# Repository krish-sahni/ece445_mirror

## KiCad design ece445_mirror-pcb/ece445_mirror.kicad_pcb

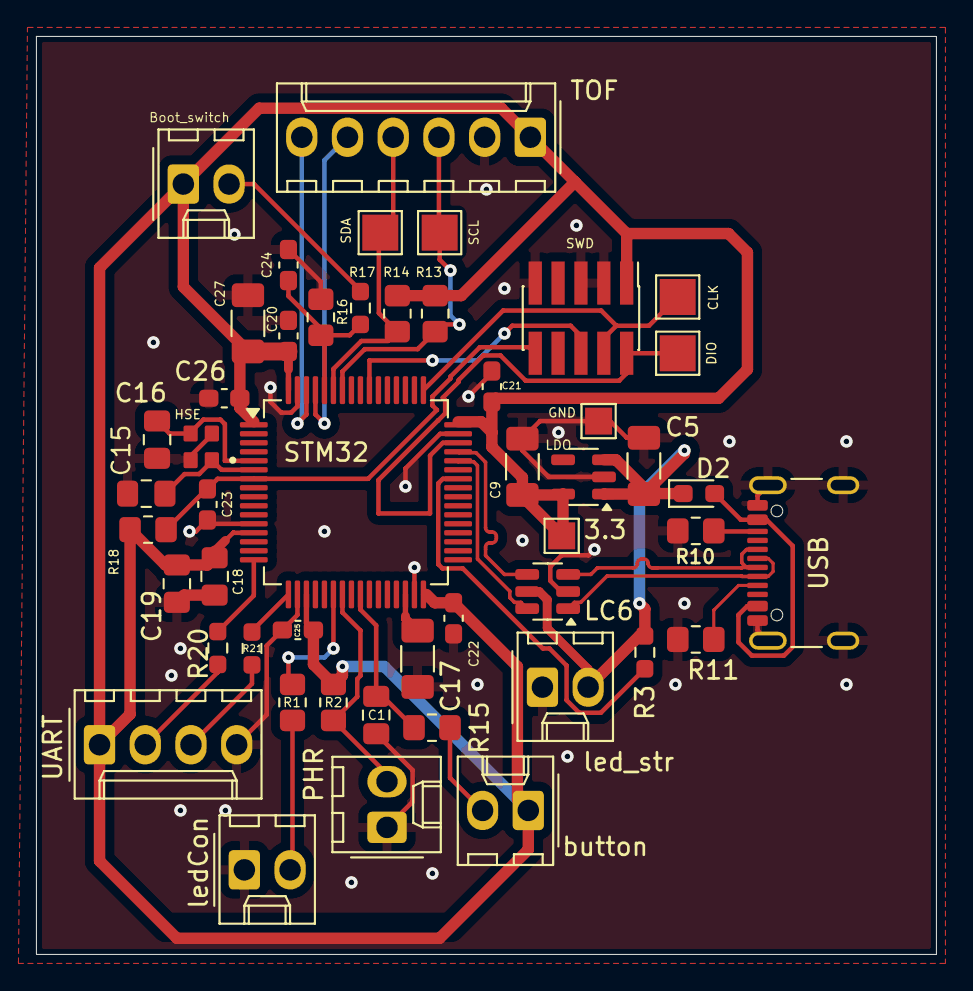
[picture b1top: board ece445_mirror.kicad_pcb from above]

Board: 2 copper layers, 50.0 x 51.0 mm, 49 parts (0 on the bottom side), 33 nets.

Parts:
3.3: TestPoint; TestPoint_Pad_1.5x1.5mm
Boot_switch: boot_switch; Molex_KK-254_AE-6410-02A_1x02_P2.54mm_Vertical
C1, C18: 1u; C_0805_2012Metric_Pad1.18x1.45mm_HandSolder
C5, C9, C27: 4.7u; C_1206_3216Metric_Pad1.33x1.80mm_HandSolder
C15, C16: 10p; C_0805_2012Metric_Pad1.18x1.45mm_HandSolder
C17: 2.2u; C_1206_3216Metric_Pad1.33x1.80mm_HandSolder
C19: 10n; C_0805_2012Metric_Pad1.18x1.45mm_HandSolder
C20, C21, C22, C23, C24, C25, C26: 100n; C_0603_1608Metric_Pad1.08x0.95mm_HandSolder
CLK: TestPoint; TestPoint_Pad_2.0x2.0mm
D2: D_Schottky; D_0603_1608Metric_Pad1.05x0.95mm_HandSolder
DIO: TestPoint; TestPoint_Pad_2.0x2.0mm
GND: TestPoint; TestPoint_Pad_1.5x1.5mm
HSE: 25MHz; OSCCC200X160X50N
LC6: USBLC6-2SC6; SOT-23-6
LDO: AP2112K-3.3; SOT-23-5
PHR: Photoresistor; Molex_KK-254_AE-6410-02A_1x02_P2.54mm_Vertical
R1, R2: 1k; R_0805_2012Metric_Pad1.20x1.40mm_HandSolder
R3, R17, R20, R21: 220R; R_0603_1608Metric_Pad0.98x0.95mm_HandSolder
R10, R11, R13, R14, R18: 5k1; R_0805_2012Metric_Pad1.20x1.40mm_HandSolder
R15, R16: 10k; R_0805_2012Metric_Pad1.20x1.40mm_HandSolder
SCL: TestPoint; TestPoint_Pad_2.0x2.0mm
SDA: TestPoint; TestPoint_Pad_2.0x2.0mm
STM32: STM32F401RBTx; LQFP-64_10x10mm_P0.5mm
SWD: Conn_ARM_JTAG_SWD_10; PinHeader_2x05_P1.27mm_Vertical_SMD
TOF: Conn_01x06; Molex_KK-254_AE-6410-06A_1x06_P2.54mm_Vertical
UART: Conn_01x04; Molex_KK-254_AE-6410-04A_1x04_P2.54mm_Vertical
USB: USB_C_Receptacle_USB2.0_14P; USB_C_Receptacle_GCT_USB4105-xx-A_16P_TopMnt_Horizontal
button: button; Molex_KK-254_AE-6410-02A_1x02_P2.54mm_Vertical
ledCon: LED_CONN; Molex_KK-254_AE-6410-02A_1x02_P2.54mm_Vertical
led_str: LED_STRIP; Molex_KK-254_AE-6410-02A_1x02_P2.54mm_Vertical

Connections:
+3.3V: 3.3.1, Boot_switch.1, C9.1, C18.1, C19.1, C20.1, C21.1, C22.1, C25.1, C26.1, C27.1, LDO.5 (VOUT), R2.2, R13.1, R14.2, R18.1, STM32.1 (VBAT), STM32.13 (VREF+), STM32.19 (VDD), STM32.32 (VDD), STM32.48 (VDD), STM32.64 (VDD), SWD.1 (VTref), TOF.1, UART.1, button.1
+5V: C5.1, D2.1 (K), LC6.5 (VBUS), LDO.1 (VIN), LDO.3 (EN), R3.1, led_str.2
/BOOT0: C24.1, R16.1, R17.1, STM32.60 (BOOT0)
/HSE_in: C16.1, HSE.3, STM32.5 (PH0)
/HSE_out: C15.1, HSE.1, STM32.6 (PH1)
/I2C_SCL: R13.2, SCL.1, STM32.58 (PB6), TOF.3
/I2C_SDA: R14.1, SDA.1, STM32.59 (PB7), TOF.4
/LED_A: R1.2, STM32.22 (PA6)
/LED_STRIP: R3.2, STM32.42 (PA9)
/SWD_CLK: CLK.1, STM32.49 (PA14), SWD.4 (SWCLK/TCK)
/SWD_DIO: DIO.1, STM32.46 (PA13), SWD.2 (SWDIO/TMS)
/SWD_NRST: C23.1, R18.2, STM32.7 (NRST), SWD.10 (~RESET)
/SWD_TRC: STM32.55 (PB3), SWD.6 (SWO/TDO)
/TOF_GPIO: STM32.62 (PB9), TOF.6
/TOF_XSHUT: STM32.61 (PB8), TOF.5
/UART_RX: R21.2, STM32.17 (PA3)
/UART_RXC: R21.1, UART.3
/UART_TX: R20.2, STM32.16 (PA2)
/UART_TXC: R20.1, UART.2
/USBC_D+: LC6.3 (I/O2), USB.A6 (D+), USB.B6 (D+)
/USBC_D-: LC6.1 (I/O1), USB.A7 (D-), USB.B7 (D-)
/USB_CC1: R11.1, USB.A5 (CC1)
/USB_CC2: R10.1, USB.B5 (CC2)
/USB_D+: LC6.4 (I/O2), STM32.45 (PA12)
/USB_D-: LC6.6 (I/O1), STM32.44 (PA11)
GND: C1.2, C5.2, C9.2, C15.2, C16.2, C17.2, C18.2, C19.2, C20.2, C21.2, C22.2, C23.2, C24.2, C25.2, C26.2, C27.2, GND.1, HSE.2, HSE.4, LC6.2 (GND), LDO.2 (GND), PHR.1, R10.2, R11.2, R16.2, STM32.12 (VSSA), STM32.18 (VSS), STM32.31 (VSS), STM32.47 (VSS), STM32.63 (VSS), SWD.3 (GND), SWD.5 (GND), SWD.9 (GNDDetect), TOF.2, UART.4, USB.A1 (GND), USB.A12 (GND), USB.B1 (GND), USB.B12 (GND), USB.S1 (SHIELD), ledCon.1, led_str.1
unnamed: D2.2 (A), USB.A4 (VBUS), USB.A9 (VBUS), USB.B4 (VBUS), USB.B9 (VBUS)
unnamed: R1.1, ledCon.2
unnamed: R15.2, button.2
unnamed: Boot_switch.2, R17.2
unnamed: PHR.2, R2.1, STM32.23 (PA7)
unnamed: C1.1, R15.1, STM32.25 (PC5)
unnamed: C17.1, STM32.30 (VCAP1)

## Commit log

2026-03-02 connor first commit
2026-03-03 added a raspberry pi version we can just port over
2026-03-04 schematic completed; changed chip; added HSE, vref+
2026-03-04 footprints!
2026-03-04 UI & cursor demo
2026-03-05 placement done
2026-03-05 fixed silkscreen
